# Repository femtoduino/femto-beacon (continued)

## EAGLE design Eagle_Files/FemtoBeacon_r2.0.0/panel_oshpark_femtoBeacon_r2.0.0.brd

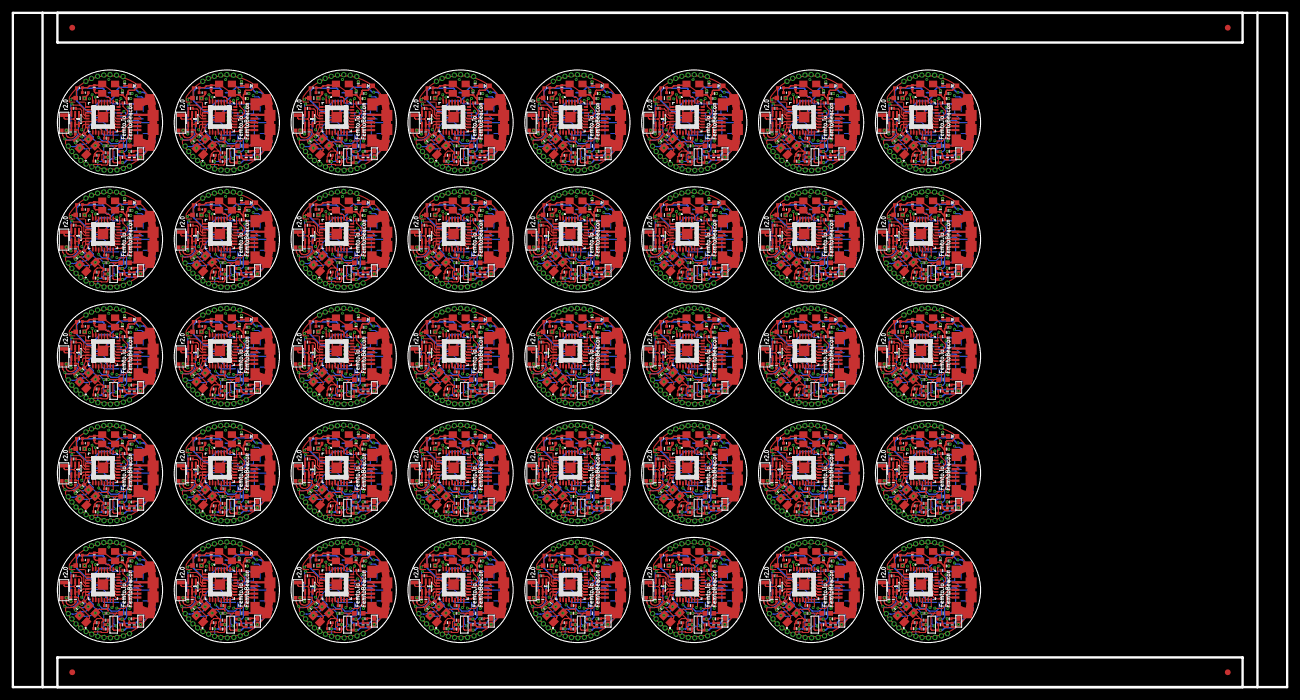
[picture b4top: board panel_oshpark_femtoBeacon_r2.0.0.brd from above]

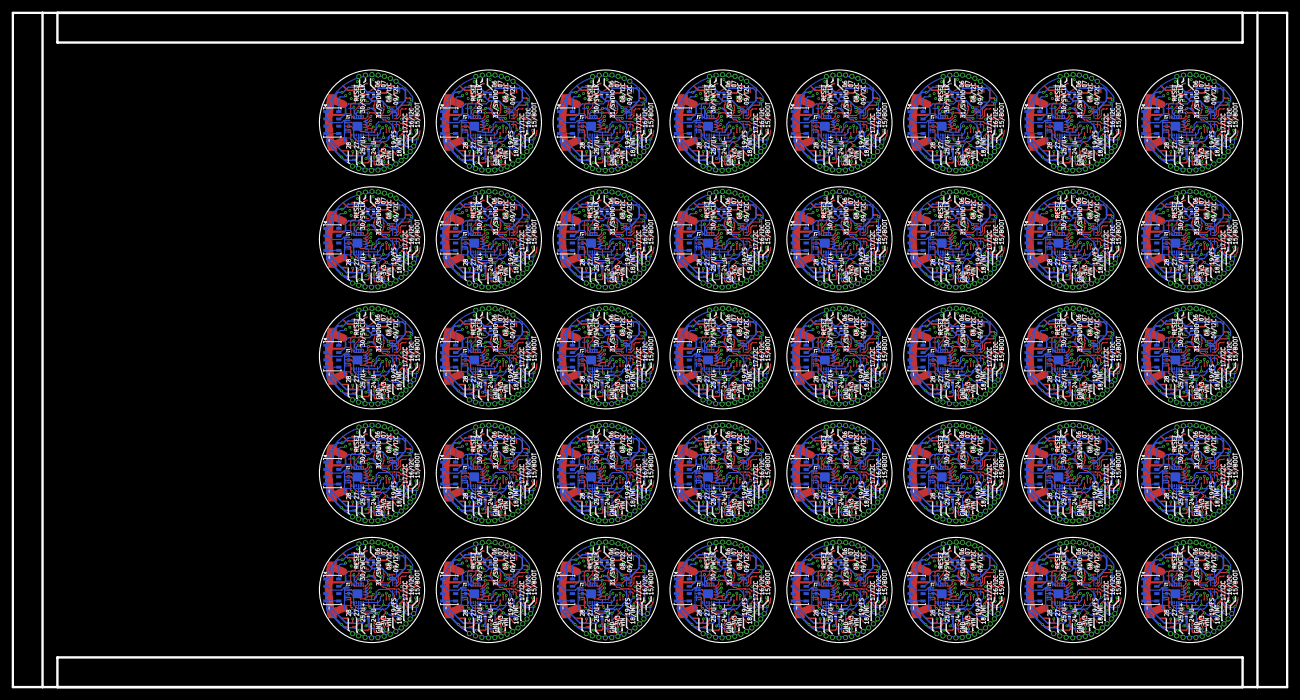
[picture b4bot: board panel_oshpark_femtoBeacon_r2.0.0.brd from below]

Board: 4 copper layers, 218.1 x 115.4 mm, 2404 parts (280 on the bottom side), 1440 nets.

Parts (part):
ANT1, ANT2, ANT3, ANT4, ANT5, ANT6, ANT7, ANT8, ANT9, ANT10, ANT11, ANT12, ANT13, ANT14, ANT15, ANT16, ANT17, ANT18, ANT19, ANT20, ANT21, ANT22, ANT23, ANT24, ANT25, ANT26, ANT27, ANT28, ANT29, ANT30, ANT31, ANT32, ANT33, ANT34, ANT35, ANT36, ANT37, ANT38, ANT39, ANT40: PULSE_ANT_2.4GHZ; ANT_BAR
BTN, BTN1, BTN2, BTN3, BTN4, BTN5, BTN6, BTN7, BTN8, BTN9, BTN10, BTN11, BTN12, BTN13, BTN14, BTN15, BTN16, BTN17, BTN18, BTN19, BTN20, BTN21, BTN22, BTN23, BTN24, BTN25, BTN26, BTN27, BTN28, BTN29, BTN30, BTN31, BTN32, BTN33, BTN34, BTN35, BTN36, BTN37, BTN38, BTN39: DNP; SPST_SMD
C1, C2, C8, C9, C10, C16, C17, C18, C19, C25, C26, C27, C28, C29, C30, C32, C33, C36, C45, C46, C47, C48, C52, C53, C54, C55, C56, C59, C68, C69, C70, C71, C75, C76, C77, C78, C79, C82, C91, C92, C93, C94, C98, C99, C100, C101, C102, C105, C114, C115, C116, C117, C121, C122, C123, C124, C125, C128, C137, C138, C139, C140, C144, C145, C146, C147, C148, C151, C160, C161, C162, C163, C167, C168, C169, C170, C171, C174, C183, C184, C185, C186, C190, C191, C192, C193, C194, C197, C206, C207, C208, C209, C213, C214, C215, C216, C217, C220, C229, C230, C231, C232, C236, C237, C238, C239, C240, C243, C252, C253, C254, C255, C259, C260, C261, C262, C263, C266, C275, C276, C277, C278, C282, C283, C284, C285, C286, C289, C298, C299, C300, C301, C305, C306, C307, C308, C309, C312, C321, C322, C323, C324, C328, C329, C330, C331, C332, C335, C344, C345, C346, C347, C351, C352, C353, C354, C355, C358, C367, C368, C369, C370, C374, C375, C376, C377, C378, C381, C390, C391, C392, C393, C397, C398, C399, C400, C401, C404, C413, C414, C415, C416, C420, C421, C422, C423, C424, C427, C436, C437, C438, C439, C443, C444, C445, C446, C447, C450, C459, C460, C461, C462, C466, C467, C468, C469, C470, C473, C482, C483, C484, C485, C489, C490, C491, C492, C493, C496, C505, C506, C507, C508, C512, C513, C514, C515, C516, C519, C528, C529, C530, C531, C535, C536, C537, C538, C539, C542, C551, C552, C553, C554, C558, C559, C560, C561, C562, C565, C574, C575, C576, C577, C581, C582, C583, C584, C585, C588, C597, C598, C599, C600, C604, C605, C606, C607, C608, C611, C620, C621, C622, C623, C627, C628, C629, C630, C631, C634, C643, C644, C645, C646, C650, C651, C652, C653, C654, C657, C666, C667, C668, C669, C673, C674, C675, C676, C677, C680, C689, C690, C691, C692, C696, C697, C698, C699, C700, C703, C712, C713, C714, C715, C719, C720, C721, C722, C723, C726, C735, C736, C737, C738, C742, C743, C744, C745, C746, C749, C758, C759, C760, C761, C765, C766, C767, C768, C769, C772, C781, C782, C783, C784, C788, C789, C790, C791, C792, C795, C804, C805, C806, C807, C811, C812, C813, C814, C815, C818, C827, C828, C829, C830, C834, C835, C836, C837, C838, C841, C850, C851, C852, C853, C857, C858, C859, C860, C861, C864, C873, C874, C875, C876, C880, C881, C882, C883, C884, C887, C896, C897, C898, C899, C903, C904, C905, C906, C907, C910, C919, C920: 0.1uF; PART
C3, C4, C37, C38, C60, C61, C83, C84, C106, C107, C129, C130, C152, C153, C175, C176, C198, C199, C221, C222, C244, C245, C267, C268, C290, C291, C313, C314, C336, C337, C359, C360, C382, C383, C405, C406, C428, C429, C451, C452, C474, C475, C497, C498, C520, C521, C543, C544, C566, C567, C589, C590, C612, C613, C635, C636, C658, C659, C681, C682, C704, C705, C727, C728, C750, C751, C773, C774, C796, C797, C819, C820, C842, C843, C865, C866, C888, C889, C911, C912: 10pF; PART
C5, C6, C20, C23, C49, C50, C72, C73, C95, C96, C118, C119, C141, C142, C164, C165, C187, C188, C210, C211, C233, C234, C256, C257, C279, C280, C302, C303, C325, C326, C348, C349, C371, C372, C394, C395, C417, C418, C440, C441, C463, C464, C486, C487, C509, C510, C532, C533, C555, C556, C578, C579, C601, C602, C624, C625, C647, C648, C670, C671, C693, C694, C716, C717, C739, C740, C762, C763, C785, C786, C808, C809, C831, C832, C854, C855, C877, C878, C900, C901: 2.2uF; PART
C7, C24, C51, C74, C97, C120, C143, C166, C189, C212, C235, C258, C281, C304, C327, C350, C373, C396, C419, C442, C465, C488, C511, C534, C557, C580, C603, C626, C649, C672, C695, C718, C741, C764, C787, C810, C833, C856, C879, C902: 0.47uF; PART
C11, C12, C39, C40, C62, C63, C85, C86, C108, C109, C131, C132, C154, C155, C177, C178, C200, C201, C223, C224, C246, C247, C269, C270, C292, C293, C315, C316, C338, C339, C361, C362, C384, C385, C407, C408, C430, C431, C453, C454, C476, C477, C499, C500, C522, C523, C545, C546, C568, C569, C591, C592, C614, C615, C637, C638, C660, C661, C683, C684, C706, C707, C729, C730, C752, C753, C775, C776, C798, C799, C821, C822, C844, C845, C867, C868, C890, C891, C913, C914: 22pF, C0G, 5%; PART
C13, C41, C64, C87, C110, C133, C156, C179, C202, C225, C248, C271, C294, C317, C340, C363, C386, C409, C432, C455, C478, C501, C524, C547, C570, C593, C616, C639, C662, C685, C708, C731, C754, C777, C800, C823, C846, C869, C892, C915: DNP; PART
C14, C15, C42, C43, C65, C66, C88, C89, C111, C112, C134, C135, C157, C158, C180, C181, C203, C204, C226, C227, C249, C250, C272, C273, C295, C296, C318, C319, C341, C342, C364, C365, C387, C388, C410, C411, C433, C434, C456, C457, C479, C480, C502, C503, C525, C526, C548, C549, C571, C572, C594, C595, C617, C618, C640, C641, C663, C664, C686, C687, C709, C710, C732, C733, C755, C756, C778, C779, C801, C802, C824, C825, C847, C848, C870, C871, C893, C894, C916, C917: 9pF; PART
C21, C22, C34, C35, C57, C58, C80, C81, C103, C104, C126, C127, C149, C150, C172, C173, C195, C196, C218, C219, C241, C242, C264, C265, C287, C288, C310, C311, C333, C334, C356, C357, C379, C380, C402, C403, C425, C426, C448, C449, C471, C472, C494, C495, C517, C518, C540, C541, C563, C564, C586, C587, C609, C610, C632, C633, C655, C656, C678, C679, C701, C702, C724, C725, C747, C748, C770, C771, C793, C794, C816, C817, C839, C840, C862, C863, C885, C886, C908, C909: 10uF; _0402MP
C31, C44, C67, C90, C113, C136, C159, C182, C205, C228, C251, C274, C297, C320, C343, C366, C389, C412, C435, C458, C481, C504, C527, C550, C573, C596, C619, C642, C665, C688, C711, C734, C757, C780, C803, C826, C849, C872, C895, C918: 10nF; PART
FB1, FB2, FB3, FB4, FB5, FB6, FB7, FB8, FB9, FB10, FB11, FB12, FB13, FB14, FB15, FB16, FB17, FB18, FB19, FB20, FB21, FB22, FB23, FB24, FB25, FB26, FB27, FB28, FB29, FB30, FB31, FB32, FB33, FB34, FB35, FB36, FB37, FB38, FB39, FB40: _0603MP
FIDUCIAL1, FIDUCIAL2, FIDUCIAL3, FIDUCIAL4: FIDUCIAL_1MM
L1, L2, L3, L4, L5, L6, L7, L8, L9, L10, L11, L12, L13, L14, L15, L16, L17, L18, L19, L20, L21, L22, L23, L24, L25, L26, L27, L28, L29, L30, L31, L32, L33, L34, L35, L36, L37, L38, L39, L40: 10uH; _0603MP
LDO_VREG, LDO_VREG1, LDO_VREG2, LDO_VREG3, LDO_VREG4, LDO_VREG5, LDO_VREG6, LDO_VREG7, LDO_VREG8, LDO_VREG9, LDO_VREG10, LDO_VREG11, LDO_VREG12, LDO_VREG13, LDO_VREG14, LDO_VREG15, LDO_VREG16, LDO_VREG17, LDO_VREG18, LDO_VREG19, LDO_VREG20, LDO_VREG21, LDO_VREG22, LDO_VREG23, LDO_VREG24, LDO_VREG25, LDO_VREG26, LDO_VREG27, LDO_VREG28, LDO_VREG29, LDO_VREG30, LDO_VREG31, LDO_VREG32, LDO_VREG33, LDO_VREG34, LDO_VREG35, LDO_VREG36, LDO_VREG37, LDO_VREG38, LDO_VREG39: MCP1700T-3302E/TT
LED1, LED2, LED3, LED4, LED5, LED6, LED7, LED8, LED9, LED10, LED11, LED12, LED13, LED14, LED15, LED16, LED17, LED18, LED19, LED20, LED21, LED22, LED23, LED24, LED25, LED26, LED27, LED28, LED29, LED30, LED31, LED32, LED33, LED34, LED35, LED36, LED37, LED38, LED39, LED40: BLUE; CHIPLED_0603_NOOUTLINE
R1, R3, R4, R6, R11, R13, R16, R18, R21, R23, R26, R28, R31, R33, R36, R38, R41, R43, R46, R48, R51, R53, R56, R58, R61, R63, R66, R68, R71, R73, R76, R78, R81, R83, R86, R88, R91, R93, R96, R98, R101, R103, R106, R108, R111, R113, R116, R118, R121, R123, R126, R128, R131, R133, R136, R138, R141, R143, R146, R148, R151, R153, R156, R158, R161, R163, R166, R168, R171, R173, R176, R178, R181, R183, R186, R188, R191, R193, R196, R198: 330; PART
R2, R5, R12, R17, R22, R27, R32, R37, R42, R47, R52, R57, R62, R67, R72, R77, R82, R87, R92, R97, R102, R107, R112, R117, R122, R127, R132, R137, R142, R147, R152, R157, R162, R167, R172, R177, R182, R187, R192, R197: 10K; PART
R7, R8, R9, R10, R14, R15, R19, R20, R24, R25, R29, R30, R34, R35, R39, R40, R44, R45, R49, R50, R54, R55, R59, R60, R64, R65, R69, R70, R74, R75, R79, R80, R84, R85, R89, R90, R94, R95, R99, R100, R104, R105, R109, R110, R114, R115, R119, R120, R124, R125, R129, R130, R134, R135, R139, R140, R144, R145, R149, R150, R154, R155, R159, R160, R164, R165, R169, R170, R174, R175, R179, R180, R184, R185, R189, R190, R194, R195, R199, R200: 2.2K; PART
SER3628CT-ND, SER3628CT-ND1, SER3628CT-ND2, SER3628CT-ND3, SER3628CT-ND4, SER3628CT-ND5, SER3628CT-ND6, SER3628CT-ND7, SER3628CT-ND8, SER3628CT-ND9, SER3628CT-ND10, SER3628CT-ND11, SER3628CT-ND12, SER3628CT-ND13, SER3628CT-ND14, SER3628CT-ND15, SER3628CT-ND16, SER3628CT-ND17, SER3628CT-ND18, SER3628CT-ND19, SER3628CT-ND20, SER3628CT-ND21, SER3628CT-ND22, SER3628CT-ND23, SER3628CT-ND24, SER3628CT-ND25, SER3628CT-ND26, SER3628CT-ND27, SER3628CT-ND28, SER3628CT-ND29, SER3628CT-ND30, SER3628CT-ND31, SER3628CT-ND32, SER3628CT-ND33, SER3628CT-ND34, SER3628CT-ND35, SER3628CT-ND36, SER3628CT-ND37, SER3628CT-ND38, SER3628CT-ND39: 16MHz; TSX-3225
TSX-3225_CRYSTAL, TSX-3225_CRYSTAL1, TSX-3225_CRYSTAL2, TSX-3225_CRYSTAL3, TSX-3225_CRYSTAL4, TSX-3225_CRYSTAL5, TSX-3225_CRYSTAL6, TSX-3225_CRYSTAL7, TSX-3225_CRYSTAL8, TSX-3225_CRYSTAL9, TSX-3225_CRYSTAL10, TSX-3225_CRYSTAL11, TSX-3225_CRYSTAL12, TSX-3225_CRYSTAL13, TSX-3225_CRYSTAL14, TSX-3225_CRYSTAL15, TSX-3225_CRYSTAL16, TSX-3225_CRYSTAL17, TSX-3225_CRYSTAL18, TSX-3225_CRYSTAL19, TSX-3225_CRYSTAL20, TSX-3225_CRYSTAL21, TSX-3225_CRYSTAL22, TSX-3225_CRYSTAL23, TSX-3225_CRYSTAL24, TSX-3225_CRYSTAL25, TSX-3225_CRYSTAL26, TSX-3225_CRYSTAL27, TSX-3225_CRYSTAL28, TSX-3225_CRYSTAL29, TSX-3225_CRYSTAL30, TSX-3225_CRYSTAL31, TSX-3225_CRYSTAL32, TSX-3225_CRYSTAL33, TSX-3225_CRYSTAL34, TSX-3225_CRYSTAL35, TSX-3225_CRYSTAL36, TSX-3225_CRYSTAL37, TSX-3225_CRYSTAL38, TSX-3225_CRYSTAL39: 48MHz; TSX-3225
U$1, U$2, U$3, U$4, U$5, U$7, U$8, U$9, U$10, U$11, U$13, U$14, U$15, U$16, U$17, U$18, U$19, U$20, U$21, U$22, U$23, U$24, U$25, U$26, U$27, U$32, U$33, U$34, U$35, U$36, U$37, U$38, U$39, U$40, U$41, U$42, U$43, U$45, U$46, U$47, U$48, U$49, U$50, U$51, U$52, U$53, U$54, U$55, U$56, U$57, U$58, U$59, U$60, U$61, U$62, U$63, U$64, U$69, U$70, U$71, U$72, U$73, U$74, U$75, U$77, U$78, U$79, U$80, U$81, U$82, U$83, U$84, U$85, U$86, U$87, U$88, U$93, U$94, U$95, U$96, U$97, U$98, U$99, U$100, U$101, U$102, U$103, U$104, U$105, U$106, U$107, U$108, U$109, U$110, U$111, U$116, U$117, U$118, U$119, U$120, U$121, U$122, U$123, U$124, U$125, U$126, U$127, U$128, U$129, U$130, U$131, U$132, U$133, U$134, U$139, U$140, U$141, U$142, U$143, U$144, U$145, U$146, U$147, U$148, U$149, U$150, U$151, U$152, U$153, U$154, U$155, U$156, U$157, U$162, U$163, U$164, U$165, U$166, U$167, U$168, U$169, U$170, U$171, U$172, U$173, U$174, U$175, U$176, U$177, U$178, U$179, U$180, U$185, U$186, U$187, U$188, U$189, U$190, U$191, U$192, U$193, U$194, U$195, U$196, U$197, U$198, U$199, U$200, U$201, U$202, U$203, U$208, U$209, U$210, U$211, U$212, U$213, U$214, U$215, U$216, U$217, U$218, U$219, U$220, U$221, U$222, U$223, U$224, U$225, U$226, U$231, U$232, U$233, U$234, U$235, U$236, U$237, U$238, U$239, U$240, U$241, U$242, U$243, U$244, U$245, U$246, U$247, U$248, U$249, U$254, U$255, U$256, U$257, U$258, U$259, U$260, U$261, U$262, U$263, U$264, U$265, U$266, U$267, U$268, U$269, U$270, U$271, U$272, U$277, U$278, U$279, U$280, U$281, U$282, U$283, U$284, U$285, U$286, U$287, U$288, U$289, U$290, U$291, U$292, U$293, U$294, U$295, U$300, U$301, U$302, U$303, U$304, U$305, U$306, U$307, U$308, U$309, U$310, U$311, U$312, U$313, U$314, U$315, U$316, U$317, U$318, U$323, U$324, U$325, U$326, U$327, U$328, U$329, U$330, U$331, U$332, U$333, U$334, U$335, U$336, U$337, U$338, U$339, U$340, U$341, U$346, U$347, U$348, U$349, U$350, U$351, U$352, U$353, U$354, U$355, U$356, U$357, U$358, U$359, U$360, U$361, U$362, U$363, U$364, U$369, U$370, U$371, U$372, U$373, U$374, U$375, U$376, U$377, U$378, U$379, U$380, U$381, U$382, U$383, U$384, U$385, U$386, U$387, U$392, U$393, U$394, U$395, U$396, U$397, U$398, U$399, U$400, U$401, U$402, U$403, U$404, U$405, U$406, U$407, U$408, U$409, U$410, U$415, U$416, U$417, U$418, U$419, U$420, U$421, U$422, U$423, U$424, U$425, U$426, U$427, U$428, U$429, U$430, U$431, U$432, U$433, U$438, U$439, U$440, U$441, U$442, U$443, U$444, U$445, U$446, U$447, U$448, U$449, U$450, U$451, U$452, U$453, U$454, U$455, U$456, U$461, U$462, U$463, U$464, U$465, U$466, U$467, U$468, U$469, U$470, U$471, U$472, U$473, U$474, U$475, U$476, U$477, U$478, U$479, U$484, U$485, U$486, U$487, U$488, U$489, U$490, U$491, U$492, U$493, U$494, U$495, U$496, U$497, U$498, U$499, U$500, U$501, U$502, U$507, U$508, U$509, U$510, U$511, U$512, U$513, U$514, U$515, U$516, U$517, U$518, U$519, U$520, U$521, U$522, U$523, U$524, U$525, U$530, U$531, U$532, U$533, U$534, U$535, U$536, U$537, U$538, U$539, U$540, U$541, U$542, U$543, U$544, U$545, U$546, U$547, U$548, U$553, U$554, U$555, U$556, U$557, U$558, U$559, U$560, U$561, U$562, U$563, U$564, U$565, U$566, U$567, U$568, U$569, U$570, U$571, U$576, U$577, U$578, U$579, U$580, U$581, U$582, U$583, U$584, U$585, U$586, U$587, U$588, U$589, U$590, U$591, U$592, U$593, U$594, U$599, U$600, U$601, U$602, U$603, U$604, U$605, U$606, U$607, U$608, U$609, U$610, U$611, U$612, U$613, U$614, U$615, U$616, U$617, U$622, U$623, U$624, U$625, U$626, U$627, U$628, U$629, U$630, U$631, U$632, U$633, U$634, U$635, U$636, U$637, U$638, U$639, U$640, U$645, U$646, U$647, U$648, U$649, U$650, U$651, U$652, U$653, U$654, U$655, U$656, U$657, U$658, U$659, U$660, U$661, U$662, U$663, U$668, U$669, U$670, U$671, U$672, U$673, U$674, U$675, U$676, U$677, U$678, U$679, U$680, U$681, U$682, U$683, U$684, U$685, U$686, U$691, U$692, U$693, U$694, U$695, U$696, U$697, U$698, U$699, U$700, U$701, U$702, U$703, U$704, U$705, U$706, U$707, U$708, U$709, U$714, U$715, U$716, U$717, U$718, U$719, U$720, U$721, U$722, U$723, U$724, U$725, U$726, U$727, U$728, U$729, U$730, U$731, U$732, U$737, U$738, U$739, U$740, U$741, U$742, U$743, U$744, U$745, U$746, U$747, U$748, U$749, U$750, U$751, U$752, U$753, U$754, U$755, U$760, U$761, U$762, U$763, U$764, U$765, U$766, U$767, U$768, U$769, U$770, U$771, U$772, U$773, U$774, U$775, U$776, U$777, U$778, U$783, U$784, U$785, U$786, U$787, U$788, U$789, U$790, U$791, U$792, U$793, U$794, U$795, U$796, U$797, U$798, U$799, U$800, U$801, U$806, U$807, U$808, U$809, U$810, U$811, U$812, U$813, U$814, U$815, U$816, U$817, U$818, U$819, U$820, U$821, U$822, U$823, U$824, U$829, U$830, U$831, U$832, U$833, U$834, U$835, U$836, U$837, U$838, U$839, U$840, U$841, U$842, U$843, U$844, U$845, U$846, U$847, U$852, U$853, U$854, U$855, U$856, U$857, U$858, U$859, U$860, U$861, U$862, U$863, U$864, U$865, U$866, U$867, U$868, U$869, U$870, U$875, U$876, U$877, U$878, U$879, U$880, U$881, U$882, U$883, U$884, U$885, U$886, U$887, U$888, U$889, U$890, U$891, U$892, U$893, U$898, U$899, U$900, U$901, U$902, U$903, U$904, U$905, U$906, U$907, U$908, U$909, U$910, U$911, U$912, U$913, U$914, U$915, U$916: 1X1_ROUND
U$6, U$31, U$68, U$92, U$115, U$138, U$161, U$184, U$207, U$230, U$253, U$276, U$299, U$322, U$345, U$368, U$391, U$414, U$437, U$460, U$483, U$506, U$529, U$552, U$575, U$598, U$621, U$644, U$667, U$690, U$713, U$736, U$759, U$782, U$805, U$828, U$851, U$874, U$897, U$920: MPU-9250; QFN_3X3MM
U$12, U$30, U$67, U$91, U$114, U$137, U$160, U$183, U$206, U$229, U$252, U$275, U$298, U$321, U$344, U$367, U$390, U$413, U$436, U$459, U$482, U$505, U$528, U$551, U$574, U$597, U$620, U$643, U$666, U$689, U$712, U$735, U$758, U$781, U$804, U$827, U$850, U$873, U$896, U$919: JOHANSON_2450BM15A0015E; 0805_BALUN
U$28, U$44, U$65, U$89, U$112, U$135, U$158, U$181, U$204, U$227, U$250, U$273, U$296, U$319, U$342, U$365, U$388, U$411, U$434, U$457, U$480, U$503, U$526, U$549, U$572, U$595, U$618, U$641, U$664, U$687, U$710, U$733, U$756, U$779, U$802, U$825, U$848, U$871, U$894, U$917: MS5611-01BA03
U$29, U$66, U$76, U$90, U$113, U$136, U$159, U$182, U$205, U$228, U$251, U$274, U$297, U$320, U$343, U$366, U$389, U$412, U$435, U$458, U$481, U$504, U$527, U$550, U$573, U$596, U$619, U$642, U$665, U$688, U$711, U$734, U$757, U$780, U$803, U$826, U$849, U$872, U$895, U$918: ATSAMR21E18A-MUT; QFN32
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
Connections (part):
3.3V: C5.1, C10.1, C16.1, C21.2, C29.1, C30.2, C31.2, L6.1, LDO_VREG.VOUT, R2.2, R8.2, R9.2, U$5.P$1, U$6.P$1, U$6.P$8, U$6.P$13, U$6.P$22, U$44.1, U$44.2, U$76.24, U$76.30
3.3V1: C20.1, C25.1, C28.1, C34.2, C36.1, C44.2, C45.2, L1.1, LDO_VREG1.VOUT, R5.2, R7.2, R10.2, U$8.P$1, U$28.1, U$28.2, U$29.24, U$29.30, U$31.P$1, U$31.P$8, U$31.P$13, U$31.P$22
3.3V2: C49.1, C52.1, C55.1, C57.2, C59.1, C67.2, C68.2, L2.1, LDO_VREG2.VOUT, R12.2, R14.2, R15.2, U$34.P$1, U$65.1, U$65.2, U$66.24, U$66.30, U$68.P$1, U$68.P$8, U$68.P$13, U$68.P$22
3.3V3: C72.1, C75.1, C78.1, C80.2, C82.1, C90.2, C91.2, L3.1, LDO_VREG3.VOUT, R17.2, R19.2, R20.2, U$71.P$1, U$89.1, U$89.2, U$90.24, U$90.30, U$92.P$1, U$92.P$8, U$92.P$13, U$92.P$22
3.3V4: C95.1, C98.1, C101.1, C103.2, C105.1, C113.2, C114.2, L4.1, LDO_VREG4.VOUT, R22.2, R24.2, R25.2, U$95.P$1, U$112.1, U$112.2, U$113.24, U$113.30, U$115.P$1, U$115.P$8, U$115.P$13, U$115.P$22
3.3V5: C118.1, C121.1, C124.1, C126.2, C128.1, C136.2, C137.2, L5.1, LDO_VREG5.VOUT, R27.2, R29.2, R30.2, U$118.P$1, U$135.1, U$135.2, U$136.24, U$136.30, U$138.P$1, U$138.P$8, U$138.P$13, U$138.P$22
3.3V6: C141.1, C144.1, C147.1, C149.2, C151.1, C159.2, C160.2, L7.1, LDO_VREG6.VOUT, R32.2, R34.2, R35.2, U$141.P$1, U$158.1, U$158.2, U$159.24, U$159.30, U$161.P$1, U$161.P$8, U$161.P$13, U$161.P$22
3.3V7: C164.1, C167.1, C170.1, C172.2, C174.1, C182.2, C183.2, L8.1, LDO_VREG7.VOUT, R37.2, R39.2, R40.2, U$164.P$1, U$181.1, U$181.2, U$182.24, U$182.30, U$184.P$1, U$184.P$8, U$184.P$13, U$184.P$22
3.3V8: C187.1, C190.1, C193.1, C195.2, C197.1, C205.2, C206.2, L9.1, LDO_VREG8.VOUT, R42.2, R44.2, R45.2, U$187.P$1, U$204.1, U$204.2, U$205.24, U$205.30, U$207.P$1, U$207.P$8, U$207.P$13, U$207.P$22
3.3V9: C210.1, C213.1, C216.1, C218.2, C220.1, C228.2, C229.2, L10.1, LDO_VREG9.VOUT, R47.2, R49.2, R50.2, U$210.P$1, U$227.1, U$227.2, U$228.24, U$228.30, U$230.P$1, U$230.P$8, U$230.P$13, U$230.P$22
3.3V10: C233.1, C236.1, C239.1, C241.2, C243.1, C251.2, C252.2, L11.1, LDO_VREG10.VOUT, R52.2, R54.2, R55.2, U$233.P$1, U$250.1, U$250.2, U$251.24, U$251.30, U$253.P$1, U$253.P$8, U$253.P$13, U$253.P$22
3.3V11: C256.1, C259.1, C262.1, C264.2, C266.1, C274.2, C275.2, L12.1, LDO_VREG11.VOUT, R57.2, R59.2, R60.2, U$256.P$1, U$273.1, U$273.2, U$274.24, U$274.30, U$276.P$1, U$276.P$8, U$276.P$13, U$276.P$22
3.3V12: C279.1, C282.1, C285.1, C287.2, C289.1, C297.2, C298.2, L13.1, LDO_VREG12.VOUT, R62.2, R64.2, R65.2, U$279.P$1, U$296.1, U$296.2, U$297.24, U$297.30, U$299.P$1, U$299.P$8, U$299.P$13, U$299.P$22
3.3V13: C302.1, C305.1, C308.1, C310.2, C312.1, C320.2, C321.2, L14.1, LDO_VREG13.VOUT, R67.2, R69.2, R70.2, U$302.P$1, U$319.1, U$319.2, U$320.24, U$320.30, U$322.P$1, U$322.P$8, U$322.P$13, U$322.P$22
3.3V14: C325.1, C328.1, C331.1, C333.2, C335.1, C343.2, C344.2, L15.1, LDO_VREG14.VOUT, R72.2, R74.2, R75.2, U$325.P$1, U$342.1, U$342.2, U$343.24, U$343.30, U$345.P$1, U$345.P$8, U$345.P$13, U$345.P$22
3.3V15: C348.1, C351.1, C354.1, C356.2, C358.1, C366.2, C367.2, L16.1, LDO_VREG15.VOUT, R77.2, R79.2, R80.2, U$348.P$1, U$365.1, U$365.2, U$366.24, U$366.30, U$368.P$1, U$368.P$8, U$368.P$13, U$368.P$22
3.3V16: C371.1, C374.1, C377.1, C379.2, C381.1, C389.2, C390.2, L17.1, LDO_VREG16.VOUT, R82.2, R84.2, R85.2, U$371.P$1, U$388.1, U$388.2, U$389.24, U$389.30, U$391.P$1, U$391.P$8, U$391.P$13, U$391.P$22
3.3V17: C394.1, C397.1, C400.1, C402.2, C404.1, C412.2, C413.2, L18.1, LDO_VREG17.VOUT, R87.2, R89.2, R90.2, U$394.P$1, U$411.1, U$411.2, U$412.24, U$412.30, U$414.P$1, U$414.P$8, U$414.P$13, U$414.P$22
3.3V18: C417.1, C420.1, C423.1, C425.2, C427.1, C435.2, C436.2, L19.1, LDO_VREG18.VOUT, R92.2, R94.2, R95.2, U$417.P$1, U$434.1, U$434.2, U$435.24, U$435.30, U$437.P$1, U$437.P$8, U$437.P$13, U$437.P$22
3.3V19: C440.1, C443.1, C446.1, C448.2, C450.1, C458.2, C459.2, L20.1, LDO_VREG19.VOUT, R97.2, R99.2, R100.2, U$440.P$1, U$457.1, U$457.2, U$458.24, U$458.30, U$460.P$1, U$460.P$8, U$460.P$13, U$460.P$22
3.3V20: C463.1, C466.1, C469.1, C471.2, C473.1, C481.2, C482.2, L21.1, LDO_VREG20.VOUT, R102.2, R104.2, R105.2, U$463.P$1, U$480.1, U$480.2, U$481.24, U$481.30, U$483.P$1, U$483.P$8, U$483.P$13, U$483.P$22
3.3V21: C486.1, C489.1, C492.1, C494.2, C496.1, C504.2, C505.2, L22.1, LDO_VREG21.VOUT, R107.2, R109.2, R110.2, U$486.P$1, U$503.1, U$503.2, U$504.24, U$504.30, U$506.P$1, U$506.P$8, U$506.P$13, U$506.P$22
3.3V22: C509.1, C512.1, C515.1, C517.2, C519.1, C527.2, C528.2, L23.1, LDO_VREG22.VOUT, R112.2, R114.2, R115.2, U$509.P$1, U$526.1, U$526.2, U$527.24, U$527.30, U$529.P$1, U$529.P$8, U$529.P$13, U$529.P$22
3.3V23: C532.1, C535.1, C538.1, C540.2, C542.1, C550.2, C551.2, L24.1, LDO_VREG23.VOUT, R117.2, R119.2, R120.2, U$532.P$1, U$549.1, U$549.2, U$550.24, U$550.30, U$552.P$1, U$552.P$8, U$552.P$13, U$552.P$22
3.3V24: C555.1, C558.1, C561.1, C563.2, C565.1, C573.2, C574.2, L25.1, LDO_VREG24.VOUT, R122.2, R124.2, R125.2, U$555.P$1, U$572.1, U$572.2, U$573.24, U$573.30, U$575.P$1, U$575.P$8, U$575.P$13, U$575.P$22
3.3V25: C578.1, C581.1, C584.1, C586.2, C588.1, C596.2, C597.2, L26.1, LDO_VREG25.VOUT, R127.2, R129.2, R130.2, U$578.P$1, U$595.1, U$595.2, U$596.24, U$596.30, U$598.P$1, U$598.P$8, U$598.P$13, U$598.P$22
3.3V26: C601.1, C604.1, C607.1, C609.2, C611.1, C619.2, C620.2, L27.1, LDO_VREG26.VOUT, R132.2, R134.2, R135.2, U$601.P$1, U$618.1, U$618.2, U$619.24, U$619.30, U$621.P$1, U$621.P$8, U$621.P$13, U$621.P$22
3.3V27: C624.1, C627.1, C630.1, C632.2, C634.1, C642.2, C643.2, L28.1, LDO_VREG27.VOUT, R137.2, R139.2, R140.2, U$624.P$1, U$641.1, U$641.2, U$642.24, U$642.30, U$644.P$1, U$644.P$8, U$644.P$13, U$644.P$22
3.3V28: C647.1, C650.1, C653.1, C655.2, C657.1, C665.2, C666.2, L29.1, LDO_VREG28.VOUT, R142.2, R144.2, R145.2, U$647.P$1, U$664.1, U$664.2, U$665.24, U$665.30, U$667.P$1, U$667.P$8, U$667.P$13, U$667.P$22
3.3V29: C670.1, C673.1, C676.1, C678.2, C680.1, C688.2, C689.2, L30.1, LDO_VREG29.VOUT, R147.2, R149.2, R150.2, U$670.P$1, U$687.1, U$687.2, U$688.24, U$688.30, U$690.P$1, U$690.P$8, U$690.P$13, U$690.P$22
3.3V30: C693.1, C696.1, C699.1, C701.2, C703.1, C711.2, C712.2, L31.1, LDO_VREG30.VOUT, R152.2, R154.2, R155.2, U$693.P$1, U$710.1, U$710.2, U$711.24, U$711.30, U$713.P$1, U$713.P$8, U$713.P$13, U$713.P$22
3.3V31: C716.1, C719.1, C722.1, C724.2, C726.1, C734.2, C735.2, L32.1, LDO_VREG31.VOUT, R157.2, R159.2, R160.2, U$716.P$1, U$733.1, U$733.2, U$734.24, U$734.30, U$736.P$1, U$736.P$8, U$736.P$13, U$736.P$22
3.3V32: C739.1, C742.1, C745.1, C747.2, C749.1, C757.2, C758.2, L33.1, LDO_VREG32.VOUT, R162.2, R164.2, R165.2, U$739.P$1, U$756.1, U$756.2, U$757.24, U$757.30, U$759.P$1, U$759.P$8, U$759.P$13, U$759.P$22
3.3V33: C762.1, C765.1, C768.1, C770.2, C772.1, C780.2, C781.2, L34.1, LDO_VREG33.VOUT, R167.2, R169.2, R170.2, U$762.P$1, U$779.1, U$779.2, U$780.24, U$780.30, U$782.P$1, U$782.P$8, U$782.P$13, U$782.P$22
3.3V34: C785.1, C788.1, C791.1, C793.2, C795.1, C803.2, C804.2, L35.1, LDO_VREG34.VOUT, R172.2, R174.2, R175.2, U$785.P$1, U$802.1, U$802.2, U$803.24, U$803.30, U$805.P$1, U$805.P$8, U$805.P$13, U$805.P$22
3.3V35: C808.1, C811.1, C814.1, C816.2, C818.1, C826.2, C827.2, L36.1, LDO_VREG35.VOUT, R177.2, R179.2, R180.2, U$808.P$1, U$825.1, U$825.2, U$826.24, U$826.30, U$828.P$1, U$828.P$8, U$828.P$13, U$828.P$22
3.3V36: C831.1, C834.1, C837.1, C839.2, C841.1, C849.2, C850.2, L37.1, LDO_VREG36.VOUT, R182.2, R184.2, R185.2, U$831.P$1, U$848.1, U$848.2, U$849.24, U$849.30, U$851.P$1, U$851.P$8, U$851.P$13, U$851.P$22
3.3V37: C854.1, C857.1, C860.1, C862.2, C864.1, C872.2, C873.2, L38.1, LDO_VREG37.VOUT, R187.2, R189.2, R190.2, U$854.P$1, U$871.1, U$871.2, U$872.24, U$872.30, U$874.P$1, U$874.P$8, U$874.P$13, U$874.P$22
3.3V38: C877.1, C880.1, C883.1, C885.2, C887.1, C895.2, C896.2, L39.1, LDO_VREG38.VOUT, R192.2, R194.2, R195.2, U$877.P$1, U$894.1, U$894.2, U$895.24, U$895.30, U$897.P$1, U$897.P$8, U$897.P$13, U$897.P$22
3.3V39: C900.1, C903.1, C906.1, C908.2, C910.1, C918.2, C919.2, L40.1, LDO_VREG39.VOUT, R197.2, R199.2, R200.2, U$900.P$1, U$917.1, U$917.2, U$918.24, U$918.30, U$920.P$1, U$920.P$8, U$920.P$13, U$920.P$22
ANT_OUT: ANT1.1, U$12.1
ANT_OUT1: ANT2.1, U$30.1
ANT_OUT2: ANT3.1, U$67.1
ANT_OUT3: ANT4.1, U$91.1
ANT_OUT4: ANT5.1, U$114.1
ANT_OUT5: ANT6.1, U$137.1
ANT_OUT6: ANT7.1, U$160.1
ANT_OUT7: ANT8.1, U$183.1
ANT_OUT8: ANT9.1, U$206.1
ANT_OUT9: ANT10.1, U$229.1
ANT_OUT10: ANT11.1, U$252.1
ANT_OUT11: ANT12.1, U$275.1
ANT_OUT12: ANT13.1, U$298.1
ANT_OUT13: ANT14.1, U$321.1
ANT_OUT14: ANT15.1, U$344.1
ANT_OUT15: ANT16.1, U$367.1
ANT_OUT16: ANT17.1, U$390.1
ANT_OUT17: ANT18.1, U$413.1
ANT_OUT18: ANT19.1, U$436.1
ANT_OUT19: ANT20.1, U$459.1
ANT_OUT20: ANT21.1, U$482.1
ANT_OUT21: ANT22.1, U$505.1
ANT_OUT22: ANT23.1, U$528.1
ANT_OUT23: ANT24.1, U$551.1
ANT_OUT24: ANT25.1, U$574.1
ANT_OUT25: ANT26.1, U$597.1
ANT_OUT26: ANT27.1, U$620.1
ANT_OUT27: ANT28.1, U$643.1
ANT_OUT28: ANT29.1, U$666.1
ANT_OUT29: ANT30.1, U$689.1
ANT_OUT30: ANT31.1, U$712.1
ANT_OUT31: ANT32.1, U$735.1
ANT_OUT32: ANT33.1, U$758.1
ANT_OUT33: ANT34.1, U$781.1
ANT_OUT34: ANT35.1, U$804.1
ANT_OUT35: ANT36.1, U$827.1
ANT_OUT36: ANT37.1, U$850.1
ANT_OUT37: ANT38.1, U$873.1
ANT_OUT38: ANT39.1, U$896.1
ANT_OUT39: ANT40.1, U$919.1
AVDD: C17.1, U$76.5
AVDD1: C33.1, U$29.5
AVDD2: C56.1, U$66.5
AVDD3: C79.1, U$90.5
AVDD4: C102.1, U$113.5
AVDD5: C125.1, U$136.5
AVDD6: C148.1, U$159.5
AVDD7: C171.1, U$182.5
AVDD8: C194.1, U$205.5
AVDD9: C217.1, U$228.5
AVDD10: C240.1, U$251.5
AVDD11: C263.1, U$274.5
AVDD12: C286.1, U$297.5
AVDD13: C309.1, U$320.5
AVDD14: C332.1, U$343.5
AVDD15: C355.1, U$366.5
AVDD16: C378.1, U$389.5
AVDD17: C401.1, U$412.5
AVDD18: C424.1, U$435.5
AVDD19: C447.1, U$458.5
AVDD20: C470.1, U$481.5
AVDD21: C493.1, U$504.5
AVDD22: C516.1, U$527.5
AVDD23: C539.1, U$550.5
AVDD24: C562.1, U$573.5
AVDD25: C585.1, U$596.5
AVDD26: C608.1, U$619.5
AVDD27: C631.1, U$642.5
AVDD28: C654.1, U$665.5
AVDD29: C677.1, U$688.5
AVDD30: C700.1, U$711.5
AVDD31: C723.1, U$734.5
AVDD32: C746.1, U$757.5
AVDD33: C769.1, U$780.5
AVDD34: C792.1, U$803.5
AVDD35: C815.1, U$826.5
AVDD36: C838.1, U$849.5
AVDD37: C861.1, U$872.5
AVDD38: C884.1, U$895.5
AVDD39: C907.1, U$918.5
DVDD: C2.1, U$76.21
DVDD1: C19.1, U$29.21
DVDD2: C48.1, U$66.21
DVDD3: C71.1, U$90.21
DVDD4: C94.1, U$113.21
DVDD5: C117.1, U$136.21
DVDD6: C140.1, U$159.21
DVDD7: C163.1, U$182.21
DVDD8: C186.1, U$205.21
DVDD9: C209.1, U$228.21
DVDD10: C232.1, U$251.21
DVDD11: C255.1, U$274.21
DVDD12: C278.1, U$297.21
DVDD13: C301.1, U$320.21
DVDD14: C324.1, U$343.21
DVDD15: C347.1, U$366.21
DVDD16: C370.1, U$389.21
DVDD17: C393.1, U$412.21
DVDD18: C416.1, U$435.21
DVDD19: C439.1, U$458.21
DVDD20: C462.1, U$481.21
DVDD21: C485.1, U$504.21
DVDD22: C508.1, U$527.21
DVDD23: C531.1, U$550.21
DVDD24: C554.1, U$573.21
DVDD25: C577.1, U$596.21
DVDD26: C600.1, U$619.21
DVDD27: C623.1, U$642.21
DVDD28: C646.1, U$665.21
DVDD29: C669.1, U$688.21
DVDD30: C692.1, U$711.21
DVDD31: C715.1, U$734.21
DVDD32: C738.1, U$757.21
DVDD33: C761.1, U$780.21
DVDD34: C784.1, U$803.21
DVDD35: C807.1, U$826.21
DVDD36: C830.1, U$849.21
DVDD37: C853.1, U$872.21
DVDD38: C876.1, U$895.21
DVDD39: C899.1, U$918.21
GND: ANT1.3, BTN.2, C1.2, C2.2, C3.1, C4.2, C5.2, C6.2, C7.2, C8.2, C9.2, C10.2, C13.2, C14.1, C15.2, C16.2, C17.2, C21.1, C22.1, C29.2, C30.1, C31.1, C32.2, FB1.2, LDO_VREG.GND, LED2.C, SER3628CT-ND.2, SER3628CT-ND.4, TSX-3225_CRYSTAL.2, TSX-3225_CRYSTAL.4, U$2.P$1, U$6.P$20, U$12.2, U$12.5, U$12.6, U$44.3, U$44.4, U$44.5, U$76.3, U$76.6, U$76.11, U$76.14, U$76.28, U$76.33
GND1: ANT2.3, BTN1.2, C18.2, C19.2, C20.2, C23.2, C24.2, C25.2, C26.2, C27.2, C28.2, C33.2, C34.1, C35.1, C36.2, C37.1, C38.2, C41.2, C42.1, C43.2, C44.1, C45.1, C46.2, FB2.2, LDO_VREG1.GND, LED1.C, SER3628CT-ND1.2, SER3628CT-ND1.4, TSX-3225_CRYSTAL1.2, TSX-3225_CRYSTAL1.4, U$4.P$1, U$28.3, U$28.4, U$28.5, U$29.3, U$29.6, U$29.11, U$29.14, U$29.28, U$29.33, U$30.2, U$30.5, U$30.6, U$31.P$20
GND2: ANT3.3, BTN2.2, C47.2, C48.2, C49.2, C50.2, C51.2, C52.2, C53.2, C54.2, C55.2, C56.2, C57.1, C58.1, C59.2, C60.1, C61.2, C64.2, C65.1, C66.2, C67.1, C68.1, C69.2, FB3.2, LDO_VREG2.GND, LED3.C, SER3628CT-ND2.2, SER3628CT-ND2.4, TSX-3225_CRYSTAL2.2, TSX-3225_CRYSTAL2.4, U$33.P$1, U$65.3, U$65.4, U$65.5, U$66.3, U$66.6, U$66.11, U$66.14, U$66.28, U$66.33, U$67.2, U$67.5, U$67.6, U$68.P$20
GND3: ANT4.3, BTN3.2, C70.2, C71.2, C72.2, C73.2, C74.2, C75.2, C76.2, C77.2, C78.2, C79.2, C80.1, C81.1, C82.2, C83.1, C84.2, C87.2, C88.1, C89.2, C90.1, C91.1, C92.2, FB4.2, LDO_VREG3.GND, LED4.C, SER3628CT-ND3.2, SER3628CT-ND3.4, TSX-3225_CRYSTAL3.2, TSX-3225_CRYSTAL3.4, U$70.P$1, U$89.3, U$89.4, U$89.5, U$90.3, U$90.6, U$90.11, U$90.14, U$90.28, U$90.33, U$91.2, U$91.5, U$91.6, U$92.P$20
GND4: ANT5.3, BTN4.2, C93.2, C94.2, C95.2, C96.2, C97.2, C98.2, C99.2, C100.2, C101.2, C102.2, C103.1, C104.1, C105.2, C106.1, C107.2, C110.2, C111.1, C112.2, C113.1, C114.1, C115.2, FB5.2, LDO_VREG4.GND, LED5.C, SER3628CT-ND4.2, SER3628CT-ND4.4, TSX-3225_CRYSTAL4.2, TSX-3225_CRYSTAL4.4, U$94.P$1, U$112.3, U$112.4, U$112.5, U$113.3, U$113.6, U$113.11, U$113.14, U$113.28, U$113.33, U$114.2, U$114.5, U$114.6, U$115.P$20
GND5: ANT6.3, BTN5.2, C116.2, C117.2, C118.2, C119.2, C120.2, C121.2, C122.2, C123.2, C124.2, C125.2, C126.1, C127.1, C128.2, C129.1, C130.2, C133.2, C134.1, C135.2, C136.1, C137.1, C138.2, FB6.2, LDO_VREG5.GND, LED6.C, SER3628CT-ND5.2, SER3628CT-ND5.4, TSX-3225_CRYSTAL5.2, TSX-3225_CRYSTAL5.4, U$117.P$1, U$135.3, U$135.4, U$135.5, U$136.3, U$136.6, U$136.11, U$136.14, U$136.28, U$136.33, U$137.2, U$137.5, U$137.6, U$138.P$20
GND6: ANT7.3, BTN6.2, C139.2, C140.2, C141.2, C142.2, C143.2, C144.2, C145.2, C146.2, C147.2, C148.2, C149.1, C150.1, C151.2, C152.1, C153.2, C156.2, C157.1, C158.2, C159.1, C160.1, C161.2, FB7.2, LDO_VREG6.GND, LED7.C, SER3628CT-ND6.2, SER3628CT-ND6.4, TSX-3225_CRYSTAL6.2, TSX-3225_CRYSTAL6.4, U$140.P$1, U$158.3, U$158.4, U$158.5, U$159.3, U$159.6, U$159.11, U$159.14, U$159.28, U$159.33, U$160.2, U$160.5, U$160.6, U$161.P$20
GND7: ANT8.3, BTN7.2, C162.2, C163.2, C164.2, C165.2, C166.2, C167.2, C168.2, C169.2, C170.2, C171.2, C172.1, C173.1, C174.2, C175.1, C176.2, C179.2, C180.1, C181.2, C182.1, C183.1, C184.2, FB8.2, LDO_VREG7.GND, LED8.C, SER3628CT-ND7.2, SER3628CT-ND7.4, TSX-3225_CRYSTAL7.2, TSX-3225_CRYSTAL7.4, U$163.P$1, U$181.3, U$181.4, U$181.5, U$182.3, U$182.6, U$182.11, U$182.14, U$182.28, U$182.33, U$183.2, U$183.5, U$183.6, U$184.P$20
GND8: ANT9.3, BTN8.2, C185.2, C186.2, C187.2, C188.2, C189.2, C190.2, C191.2, C192.2, C193.2, C194.2, C195.1, C196.1, C197.2, C198.1, C199.2, C202.2, C203.1, C204.2, C205.1, C206.1, C207.2, FB9.2, LDO_VREG8.GND, LED9.C, SER3628CT-ND8.2, SER3628CT-ND8.4, TSX-3225_CRYSTAL8.2, TSX-3225_CRYSTAL8.4, U$186.P$1, U$204.3, U$204.4, U$204.5, U$205.3, U$205.6, U$205.11, U$205.14, U$205.28, U$205.33, U$206.2, U$206.5, U$206.6, U$207.P$20
GND9: ANT10.3, BTN9.2, C208.2, C209.2, C210.2, C211.2, C212.2, C213.2, C214.2, C215.2, C216.2, C217.2, C218.1, C219.1, C220.2, C221.1, C222.2, C225.2, C226.1, C227.2, C228.1, C229.1, C230.2, FB10.2, LDO_VREG9.GND, LED10.C, SER3628CT-ND9.2, SER3628CT-ND9.4, TSX-3225_CRYSTAL9.2, TSX-3225_CRYSTAL9.4, U$209.P$1, U$227.3, U$227.4, U$227.5, U$228.3, U$228.6, U$228.11, U$228.14, U$228.28, U$228.33, U$229.2, U$229.5, U$229.6, U$230.P$20
GND10: ANT11.3, BTN10.2, C231.2, C232.2, C233.2, C234.2, C235.2, C236.2, C237.2, C238.2, C239.2, C240.2, C241.1, C242.1, C243.2, C244.1, C245.2, C248.2, C249.1, C250.2, C251.1, C252.1, C253.2, FB11.2, LDO_VREG10.GND, LED11.C, SER3628CT-ND10.2, SER3628CT-ND10.4, TSX-3225_CRYSTAL10.2, TSX-3225_CRYSTAL10.4, U$232.P$1, U$250.3, U$250.4, U$250.5, U$251.3, U$251.6, U$251.11, U$251.14, U$251.28, U$251.33, U$252.2, U$252.5, U$252.6, U$253.P$20
GND11: ANT12.3, BTN11.2, C254.2, C255.2, C256.2, C257.2, C258.2, C259.2, C260.2, C261.2, C262.2, C263.2, C264.1, C265.1, C266.2, C267.1, C268.2, C271.2, C272.1, C273.2, C274.1, C275.1, C276.2, FB12.2, LDO_VREG11.GND, LED12.C, SER3628CT-ND11.2, SER3628CT-ND11.4, TSX-3225_CRYSTAL11.2, TSX-3225_CRYSTAL11.4, U$255.P$1, U$273.3, U$273.4, U$273.5, U$274.3, U$274.6, U$274.11, U$274.14, U$274.28, U$274.33, U$275.2, U$275.5, U$275.6, U$276.P$20
GND12: ANT13.3, BTN12.2, C277.2, C278.2, C279.2, C280.2, C281.2, C282.2, C283.2, C284.2, C285.2, C286.2, C287.1, C288.1, C289.2, C290.1, C291.2, C294.2, C295.1, C296.2, C297.1, C298.1, C299.2, FB13.2, LDO_VREG12.GND, LED13.C, SER3628CT-ND12.2, SER3628CT-ND12.4, TSX-3225_CRYSTAL12.2, TSX-3225_CRYSTAL12.4, U$278.P$1, U$296.3, U$296.4, U$296.5, U$297.3, U$297.6, U$297.11, U$297.14, U$297.28, U$297.33, U$298.2, U$298.5, U$298.6, U$299.P$20
GND13: ANT14.3, BTN13.2, C300.2, C301.2, C302.2, C303.2, C304.2, C305.2, C306.2, C307.2, C308.2, C309.2, C310.1, C311.1, C312.2, C313.1, C314.2, C317.2, C318.1, C319.2, C320.1, C321.1, C322.2, FB14.2, LDO_VREG13.GND, LED14.C, SER3628CT-ND13.2, SER3628CT-ND13.4, TSX-3225_CRYSTAL13.2, TSX-3225_CRYSTAL13.4, U$301.P$1, U$319.3, U$319.4, U$319.5, U$320.3, U$320.6, U$320.11, U$320.14, U$320.28, U$320.33, U$321.2, U$321.5, U$321.6, U$322.P$20
GND14: ANT15.3, BTN14.2, C323.2, C324.2, C325.2, C326.2, C327.2, C328.2, C329.2, C330.2, C331.2, C332.2, C333.1, C334.1, C335.2, C336.1, C337.2, C340.2, C341.1, C342.2, C343.1, C344.1, C345.2, FB15.2, LDO_VREG14.GND, LED15.C, SER3628CT-ND14.2, SER3628CT-ND14.4, TSX-3225_CRYSTAL14.2, TSX-3225_CRYSTAL14.4, U$324.P$1, U$342.3, U$342.4, U$342.5, U$343.3, U$343.6, U$343.11, U$343.14, U$343.28, U$343.33, U$344.2, U$344.5, U$344.6, U$345.P$20
GND15: ANT16.3, BTN15.2, C346.2, C347.2, C348.2, C349.2, C350.2, C351.2, C352.2, C353.2, C354.2, C355.2, C356.1, C357.1, C358.2, C359.1, C360.2, C363.2, C364.1, C365.2, C366.1, C367.1, C368.2, FB16.2, LDO_VREG15.GND, LED16.C, SER3628CT-ND15.2, SER3628CT-ND15.4, TSX-3225_CRYSTAL15.2, TSX-3225_CRYSTAL15.4, U$347.P$1, U$365.3, U$365.4, U$365.5, U$366.3, U$366.6, U$366.11, U$366.14, U$366.28, U$366.33, U$367.2, U$367.5, U$367.6, U$368.P$20
GND16: ANT17.3, BTN16.2, C369.2, C370.2, C371.2, C372.2, C373.2, C374.2, C375.2, C376.2, C377.2, C378.2, C379.1, C380.1, C381.2, C382.1, C383.2, C386.2, C387.1, C388.2, C389.1, C390.1, C391.2, FB17.2, LDO_VREG16.GND, LED17.C, SER3628CT-ND16.2, SER3628CT-ND16.4, TSX-3225_CRYSTAL16.2, TSX-3225_CRYSTAL16.4, U$370.P$1, U$388.3, U$388.4, U$388.5, U$389.3, U$389.6, U$389.11, U$389.14, U$389.28, U$389.33, U$390.2, U$390.5, U$390.6, U$391.P$20
GND17: ANT18.3, BTN17.2, C392.2, C393.2, C394.2, C395.2, C396.2, C397.2, C398.2, C399.2, C400.2, C401.2, C402.1, C403.1, C404.2, C405.1, C406.2, C409.2, C410.1, C411.2, C412.1, C413.1, C414.2, FB18.2, LDO_VREG17.GND, LED18.C, SER3628CT-ND17.2, SER3628CT-ND17.4, TSX-3225_CRYSTAL17.2, TSX-3225_CRYSTAL17.4, U$393.P$1, U$411.3, U$411.4, U$411.5, U$412.3, U$412.6, U$412.11, U$412.14, U$412.28, U$412.33, U$413.2, U$413.5, U$413.6, U$414.P$20
GND18: ANT19.3, BTN18.2, C415.2, C416.2, C417.2, C418.2, C419.2, C420.2, C421.2, C422.2, C423.2, C424.2, C425.1, C426.1, C427.2, C428.1, C429.2, C432.2, C433.1, C434.2, C435.1, C436.1, C437.2, FB19.2, LDO_VREG18.GND, LED19.C, SER3628CT-ND18.2, SER3628CT-ND18.4, TSX-3225_CRYSTAL18.2, TSX-3225_CRYSTAL18.4, U$416.P$1, U$434.3, U$434.4, U$434.5, U$435.3, U$435.6, U$435.11, U$435.14, U$435.28, U$435.33, U$436.2, U$436.5, U$436.6, U$437.P$20
GND19: ANT20.3, BTN19.2, C438.2, C439.2, C440.2, C441.2, C442.2, C443.2, C444.2, C445.2, C446.2, C447.2, C448.1, C449.1, C450.2, C451.1, C452.2, C455.2, C456.1, C457.2, C458.1, C459.1, C460.2, FB20.2, LDO_VREG19.GND, LED20.C, SER3628CT-ND19.2, SER3628CT-ND19.4, TSX-3225_CRYSTAL19.2, TSX-3225_CRYSTAL19.4, U$439.P$1, U$457.3, U$457.4, U$457.5, U$458.3, U$458.6, U$458.11, U$458.14, U$458.28, U$458.33, U$459.2, U$459.5, U$459.6, U$460.P$20
GND20: ANT21.3, BTN20.2, C461.2, C462.2, C463.2, C464.2, C465.2, C466.2, C467.2, C468.2, C469.2, C470.2, C471.1, C472.1, C473.2, C474.1, C475.2, C478.2, C479.1, C480.2, C481.1, C482.1, C483.2, FB21.2, LDO_VREG20.GND, LED21.C, SER3628CT-ND20.2, SER3628CT-ND20.4, TSX-3225_CRYSTAL20.2, TSX-3225_CRYSTAL20.4, U$462.P$1, U$480.3, U$480.4, U$480.5, U$481.3, U$481.6, U$481.11, U$481.14, U$481.28, U$481.33, U$482.2, U$482.5, U$482.6, U$483.P$20
GND21: ANT22.3, BTN21.2, C484.2, C485.2, C486.2, C487.2, C488.2, C489.2, C490.2, C491.2, C492.2, C493.2, C494.1, C495.1, C496.2, C497.1, C498.2, C501.2, C502.1, C503.2, C504.1, C505.1, C506.2, FB22.2, LDO_VREG21.GND, LED22.C, SER3628CT-ND21.2, SER3628CT-ND21.4, TSX-3225_CRYSTAL21.2, TSX-3225_CRYSTAL21.4, U$485.P$1, U$503.3, U$503.4, U$503.5, U$504.3, U$504.6, U$504.11, U$504.14, U$504.28, U$504.33, U$505.2, U$505.5, U$505.6, U$506.P$20
GND22: ANT23.3, BTN22.2, C507.2, C508.2, C509.2, C510.2, C511.2, C512.2, C513.2, C514.2, C515.2, C516.2, C517.1, C518.1, C519.2, C520.1, C521.2, C524.2, C525.1, C526.2, C527.1, C528.1, C529.2, FB23.2, LDO_VREG22.GND, LED23.C, SER3628CT-ND22.2, SER3628CT-ND22.4, TSX-3225_CRYSTAL22.2, TSX-3225_CRYSTAL22.4, U$508.P$1, U$526.3, U$526.4, U$526.5, U$527.3, U$527.6, U$527.11, U$527.14, U$527.28, U$527.33, U$528.2, U$528.5, U$528.6, U$529.P$20
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
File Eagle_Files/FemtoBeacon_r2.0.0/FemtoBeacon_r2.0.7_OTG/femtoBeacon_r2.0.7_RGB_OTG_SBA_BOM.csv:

##########################################################################
       Name: Placement Bill of Materials Generator

    Version: 4 (2-sided, top)
         By: Small Batch Assembly
        URL: www.smallbatchassembly.com
 SourceFile: femtoBeacon_r2.0.7_RGB_OTG.brd
   DateTime: 11/24/17 7:52 PM
      Units: inches
##########################################################################
REF,PACKAGE,VALUE,X,Y,ROTATION,
ANT_SMD   , 0479480001            , 0479480001     , 0.2137, 0.5543, 180.0
BALUN   , 0805_BALUN            , JOHANSON_2450BM15A0015E     , 0.3937, 0.5770, 270.0
BTN   , SPST_SMD            , DNP     , 0.8398, 0.3440, 270.0
C1   , PART            , 0.1uF     , 0.7968, 0.3190, 270.0
C2   , PART            , 0.1uF     , 0.6077, 0.4490, 0.0
C5   , _0402MP            , 2.2uF     , 0.7167, 0.3200, 180.0
C6   , _0402MP            , 2.2uF     , 0.5987, 0.3510, 180.0
C7   , PART            , 0.47uF     , 0.6047, 0.2910, 180.0
C8   , PART            , 0.1uF     , 0.7687, 0.7430, 180.0
C9   , PART            , 0.1uF     , 0.7318, 0.6870, 0.0
C10   , PART            , 0.1uF     , 0.5397, 0.3240, 180.0
C11   , _0402MP            , 1.2pF     , 0.3850, 0.4650, 0.0
C12   , PART            , 22pF     , 0.3937, 0.6550, 180.0
C13   , PART            , DNP     , 0.3900, 0.4350, 0.0
C14   , PART            , 9pF     , 0.5277, 0.7920, 270.0
C15   , PART            , 9pF     , 0.7167, 0.7550, 270.0
C16   , PART            , 0.1uF     , 0.6067, 0.3975, 0.0
C17   , PART            , 0.1uF     , 0.7587, 0.7160, 180.0
C21   , _0402MP            , 10uF     , 0.4267, 0.7890, 180.0
C22   , _0402MP            , 10uF     , 0.4667, 0.7560, 0.0
C31   , PART            , 10nF     , 0.5357, 0.2940, 0.0
FB1   , _0603MP            , Ferrite     , 0.7347, 0.3970, 180.0
FID1   , FIDUCIAL_1MM            , FIDUCIAL     , 0.1000, 0.3000, 0.0
FID2   , FIDUCIAL_1MM            , FIDUCIAL     , 0.1000, 0.8000, 0.0
FID3   , FIDUCIAL_1MM            , FIDUCIAL     , 1.2000, 0.8000, 0.0
IC   , QFN32            , ATSAMR21E18A-MUT     , 0.5861, 0.5907, 270.0
L1   , _0603MP            , 1.8nH     , 0.3300, 0.4650, 270.0
L6   , _0603MP            , 10uH     , 0.4317, 0.7190, 0.0
LDO_VREG   , MCP1700T-3302E/TT            , MCP1700T-3302E/TT     , 0.6581, 0.3211, 90.0
R1   , PART            , 330     , 0.7767, 0.3600, 180.0
R2   , PART            , 10K     , 0.7637, 0.3190, 270.0
R4   , PART            , 330     , 0.7760, 0.7880, 0.0
R5   , PART            , 330     , 0.7350, 0.5600, 0.0
R6   , PART            , 330     , 0.7700, 0.8150, 0.0
R7   , PART            , 330     , 0.7800, 0.8450, 0.0
R10   , PART            , 100K     , 0.7750, 0.6140, 90.0
RGBLED   , LRTB_R48G            , LRTB_R48G     , 0.8300, 0.7950, 270.0
USB   , USB_MICROB_PACKAGE            , USB_MICROB     , 0.8764, 0.5550, 90.0
XOSCRF   , TSX-3225            , 16MHz     , 0.6240, 0.7825, 0.0
